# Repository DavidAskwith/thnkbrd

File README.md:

# THNKBRD

- Build command `ergogen ./ && mv output/pcbs/pcbboard.kicad_pcb kicad`

## Minor routing problems discovered post print

- The wiring for the TRRS connector is connected to to many pins
    - It only needs to be wired on a single side..

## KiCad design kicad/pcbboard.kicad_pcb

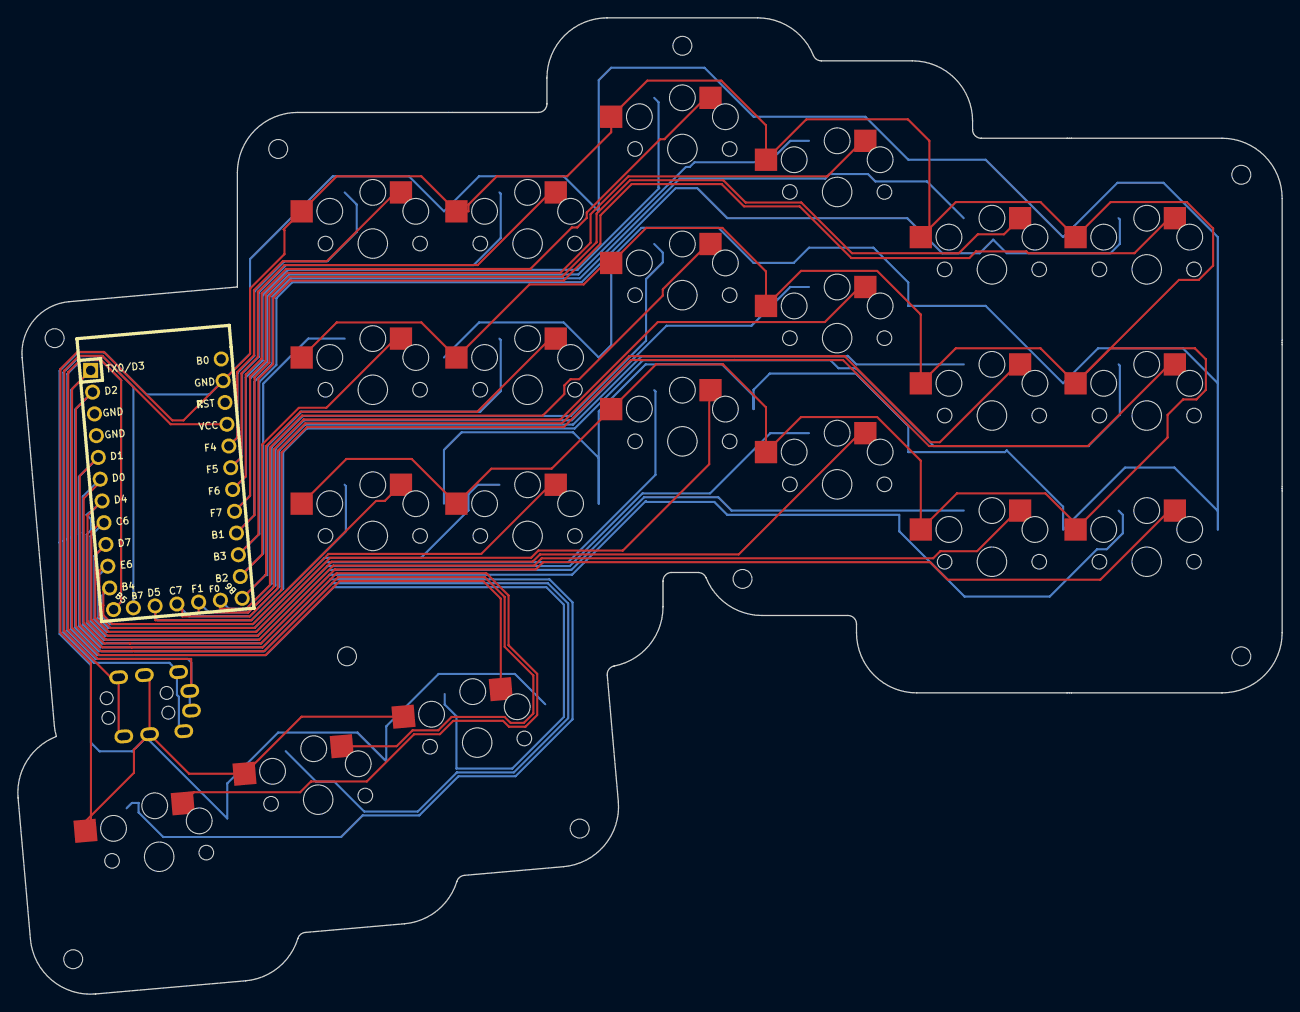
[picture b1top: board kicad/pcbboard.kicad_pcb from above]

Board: 2 copper layers, 147.0 x 113.5 mm, 32 parts (0 on the bottom side), 25 nets.

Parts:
MCU1: Elite-C
S1, S2, S3, S4, S5, S6, S7, S8, S9, S10, S11, S12, S13, S14, S15, S16, S17, S18, S19, S20, S21: PG1350
TRRS1: TRRS-PJ-320A-dual
_1, _2, _3, _4, _5, _6, _7, _8, _9: MountingHole_2.2mm_M2

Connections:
B5: MCU1.12, TRRS1.1
B7: MCU1.25, TRRS1.2
GND: MCU1.3, MCU1.4, MCU1.23, S1.2, S2.2, S3.2, S4.2, S5.2, S6.2, S7.2, S8.2, S9.2, S10.2, S11.2, S12.2, S13.2, S14.2, S15.2, S16.2, S17.2, S18.2, S19.2, S20.2, S21.2, TRRS1.3
VCC: MCU1.21, TRRS1.4
matrix_inner_bottom: MCU1.11, S1.1
matrix_inner_center: MCU1.14, S2.1
matrix_inner_top: MCU1.20, S3.1
matrix_middle_bottom: MCU1.9, S7.1
matrix_middle_center: MCU1.29, S8.1
matrix_middle_top: MCU1.18, S9.1
matrix_outer_bottom: MCU1.6, S16.1
matrix_outer_center: MCU1.26, S17.1
matrix_outer_top: MCU1.15, S18.1
matrix_pinky_bottom: MCU1.7, S13.1
matrix_pinky_center: MCU1.27, S14.1
matrix_pinky_top: MCU1.16, S15.1
matrix_pointer_bottom: MCU1.10, S4.1
matrix_pointer_center: MCU1.13, S5.1
matrix_pointer_top: MCU1.19, S6.1
matrix_ring_bottom: MCU1.8, S10.1
matrix_ring_center: MCU1.28, S11.1
matrix_ring_top: MCU1.17, S12.1
thumb_left: MCU1.5, S19.1
thumb_middle: MCU1.2, S20.1
thumb_right: MCU1.1, S21.1

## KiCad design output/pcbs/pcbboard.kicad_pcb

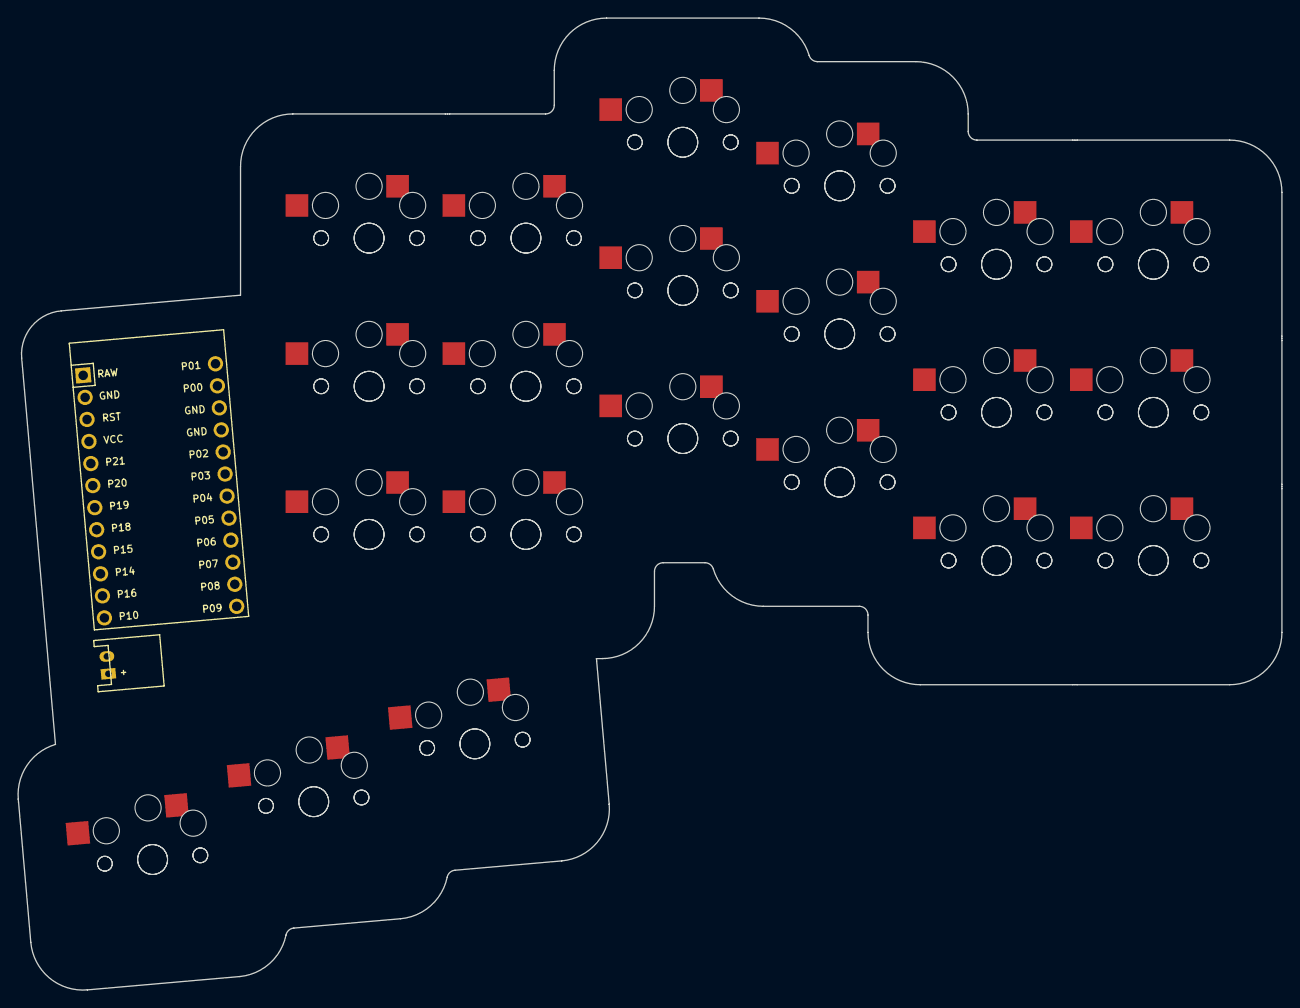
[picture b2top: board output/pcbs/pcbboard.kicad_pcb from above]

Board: 2 copper layers, 145.0 x 111.5 mm, 44 parts (0 on the bottom side), 23 nets, no tracks yet.

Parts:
JST1: JST_PH_S2B-PH-K_02x2.00mm_Angled
MCU1: ProMicro
S1, S2, S3, S4, S5, S6, S7, S8, S9, S10, S11, S12, S13, S14, S15, S16, S17, S18, S19, S20, S21, S22, S23, S24, S25, S26, S27, S28, S29, S30, S31, S32, S33, S34, S35, S36, S37, S38, S39, S40, S41, S42: PG1350

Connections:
GND: JST1.2, MCU1.2, MCU1.15, MCU1.16, S1.1, S2.1, S3.1, S4.1, S5.1, S6.1, S7.1, S8.1, S9.1, S10.1, S11.1, S12.1, S13.1, S14.1, S15.1, S16.1, S17.1, S18.1, S19.1, S20.1, S21.1, S22.1, S23.1, S24.1, S25.1, S26.1, S27.1, S28.1, S29.1, S30.1, S31.1, S32.1, S33.1, S34.1, S35.1, S36.1, S37.1, S38.1, S39.1, S40.1, S41.1, S42.1
VCC: JST1.1, MCU1.4
matrix_inner_bottom: MCU1.12, S1.2, S22.2
matrix_inner_center: S2.2, S23.2
matrix_inner_top: MCU1.24, S3.2, S24.2
matrix_middle_bottom: MCU1.10, S7.2, S28.2
matrix_middle_center: S8.2, S29.2
matrix_middle_top: MCU1.22, S9.2, S30.2
matrix_outer_bottom: MCU1.8, S16.2, S37.2
matrix_outer_center: S17.2, S38.2
matrix_outer_top: MCU1.20, S18.2, S39.2
matrix_pinky_bottom: S13.2, S34.2
matrix_pinky_center: S14.2, S35.2
matrix_pinky_top: S15.2, S36.2
matrix_pointer_bottom: MCU1.11, S4.2, S25.2
matrix_pointer_center: S5.2, S26.2
matrix_pointer_top: MCU1.23, S6.2, S27.2
matrix_ring_bottom: MCU1.9, S10.2, S31.2
matrix_ring_center: S11.2, S32.2
matrix_ring_top: MCU1.21, S12.2, S33.2
thumb_left: MCU1.5, S19.2, S40.2
thumb_middle: MCU1.6, S20.2, S41.2
thumb_right: MCU1.7, S21.2, S42.2

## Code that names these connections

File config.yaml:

units:
  # Proxy Spacing Variables
  kx: cx
  ky: cy
  # Padding Variables
  px: kx + 5
  py: ky + 5
points:
  zones:
    matrix:
      key:
        padding: 1ky
        spread: 1kx
      columns:
        inner.key:
        pointer.key:
        middle.key:
            stagger: 11
        ring.key:
            stagger: -5
        pinky.key:
            stagger: -9
        outer.key:
      rows:
        bottom:
        center:
        top:
    thumb:
      anchor:
        ref: matrix_inner_bottom
        shift: [-28, -20]
      columns:
        left.key:
          stagger: -15
        middle.key:
          stagger: 5
        right.key:
          stagger: 5
      rotate: 5
outlines:
  # comment for prod
  keys:
    - what: rectangle
      where: true
      size: [kx-0.5,ky-0.5]
  board:
    - what: outline
      name: keys
      fillet: 1
      expand: 7
    - what: rectangle
      size: [50, 55]
      corner: 6
      where:
        ref: matrix_inner_bottom
        shift: [-14, 1.5]
        rotate: 5
  # comment for prod
  combo:
    - name: board
    - operation: subtract
      name: keys
pcbs:
  pcbboard:
    outlines:
      matrix:
        outline: board
    footprints:
      choc_hotswap:
        what: choc
        where: true
        params:
          keycaps: true
          reverse: true
          hotswap: true
          from: "{{name}}"
          to: GND
      trrs: 
        what: trrs
        params:
          reverse: true
          A: B5 # Bad pin placement should be at end
          B: B7 # Bad pin placement should be at end
          C: GND
          D: VCC
        where: 
          ref: matrix_inner_bottom
          shift: [-33, -18]
          rotate: 95
      bottom_left_mount:
        what: mountinghole
        where:
          ref: thumb_left
          shift: [-11, -11]
      bottom_middle_mount:
        what: mountinghole
        where:
          ref: matrix_ring_bottom
          shift: [-11, -11]
      bottom_middle_right_mount:
        what: mountinghole
        where:
          ref: thumb_right
          shift: [11, -11]
      bottom_right_mount:
        what: mountinghole
        where:
          ref: matrix_outer_bottom
          shift: [11, -11]
      top_right_mount:
        what: mountinghole
        where:
          ref: matrix_outer_top
          shift: [11, 11]
      top_middle_moount:
        what: mountinghole
        where:
          ref: matrix_middle_top
          shift: [0, 12]
      top_left_mount:
        what: mountinghole
        where:
          ref: matrix_inner_top
          shift: [-11, 11]
      between_thumb_pcb_mount:
        what: mountinghole
        where:
          ref: matrix_inner_bottom
          shift: [-3, -14]
      left_center_mount:
        what: mountinghole
        where:
          ref: matrix_inner_center
          shift: [-37, 6]
      rp2040_elite:
        what: elite
        params:
          # GND:
          # VCC:used for trrs
          # ST: 
          D3: thumb_right
          D2: thumb_middle 
          D1: thumb_left
          D0: matrix_outer_bottom
          D4: matrix_pinky_bottom
          C6: matrix_ring_bottom
          D7: matrix_middle_bottom
          E6: matrix_pointer_bottom
          B4: matrix_inner_bottom
          # B5: used for trrs
          # B7: used for trrs 
          D5: matrix_outer_center
          C7: matrix_pinky_center
          F1: matrix_ring_center
          F0: matrix_middle_center
          B6: matrix_pointer_center
          B2: matrix_inner_center
          B3: matrix_outer_top
          B1: matrix_pinky_top 
          F7: matrix_ring_top
          F6: matrix_middle_top
          F5: matrix_pointer_top
          F4: matrix_inner_top
          # B0: not used
        where:
          ref: matrix_inner_bottom
          shift: [-24,6]
          rotate: -85

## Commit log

2024-05-25 Initial commit of board design
2024-05-25 Added pcb config
2024-05-27 pcb initial design
2024-06-04 net completed
2024-06-08 Modified config to work without a sub-module
2024-06-16 Removed pi pico config
    - Replaced with elite c footprint for use with the rp2040 pro micro
2024-06-25 PCB redesign
2024-08-29 Routing checkpoint commit
2025-03-16 Custom configuration for a QMK keyboard
2025-03-19 Port key mappings from moonlander
2025-03-19 Fix tapdance mapping
2025-05-04 Final changes pre-print
2025-05-04 Allow for permissive hold
2025-10-10 Added some ctrl improvements for layers
2025-10-15 Add script and info for flashing
2026-02-10 Vibe code a keymap visualizer
2026-02-10 Create simple mapping visualizer
2026-02-14 site: key usage indication partially working
